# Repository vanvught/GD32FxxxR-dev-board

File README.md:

[PayPal.Me Donate](https://paypal.me/AvanVught?locale.x=nl_NL)

-----------

# GD32F103R GD32F107R GD32F207R GD32F303R GD32F407R development board

This board can be used with the `GD32F103Rx`,  `GD32F303Rx` and the `GD32F107Rx` , `GD32F207Rx`, `GD32F407Rx` (Ethernet) MCU's. 

Please note that the crystal for the `GD32F107Rx`, `GD32F207Rx` and the `GD32F407Rx` is `25MHz` and the crystal for the `GD32F103Rx` and the  `GD32F303Rx` is `8MHz`.

The 2x13 header is pin compatible with the Orange Pi Zero and Raspberry Pi boards. 

Details -> [https://www.gd32-dmx.org/dev-board.html](https://www.gd32-dmx.org/dev-board.html)

# Add-on
Pixel 8x 4 Universes for the `GD32F207RG` / `GD32F407RE`

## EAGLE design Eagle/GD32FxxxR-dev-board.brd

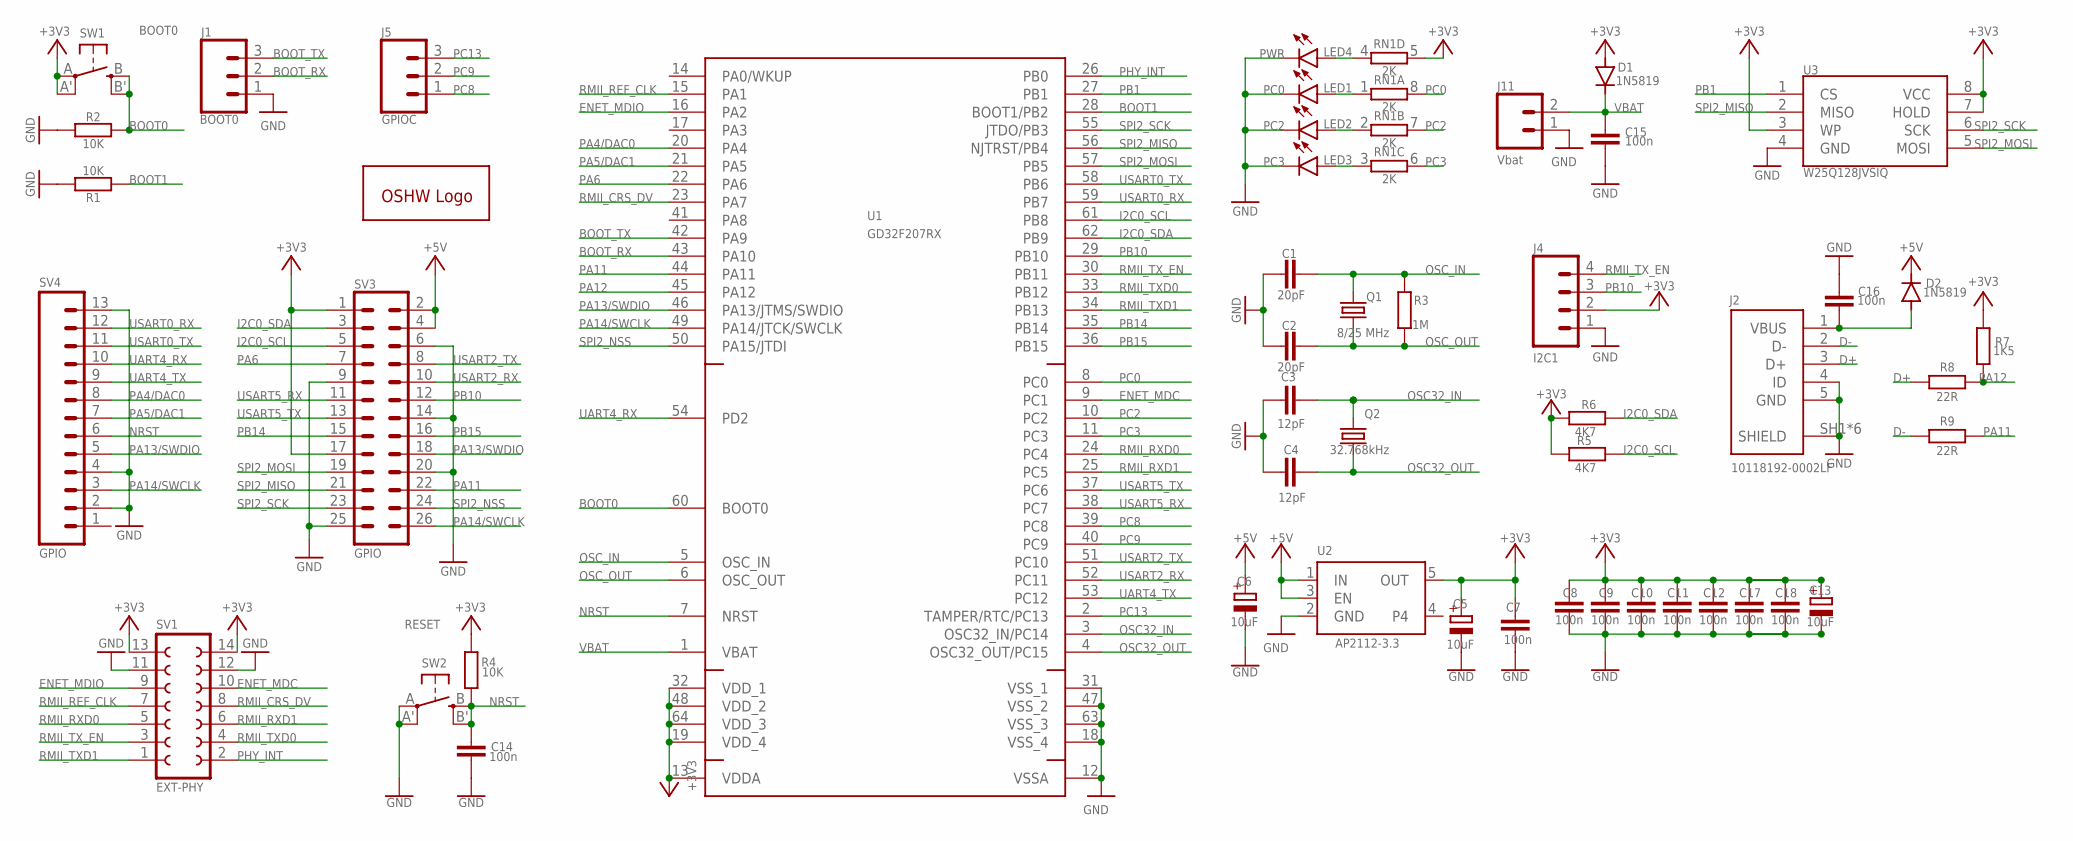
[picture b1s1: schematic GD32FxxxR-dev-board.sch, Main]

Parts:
C1, C2: 20pF; C0603; JLCPCB C38523
C3, C4: 12pF; C0603; JLCPCB C38523
C5, C6, C13: 10uF; A/3216-18R; JLCPCB C7171
C7, C8, C9, C10, C11, C12, C14, C15, C16, C17, C18: 100n; C0603; JLCPCB C14663
D1, D2: 1N5819; SOD323-R; JLCPCB C191023
GOLD_ORB_SM1: OSHWLOGOLOGO5MM; OSHW_5MM
J1: BOOT0; 1X03
J2: 10118192-0002LF; JLCPCB C2972784
J4: I2C1; 1X04
J5: GPIOC; 1X03
J11: Vbat; 1X02_NO_SILK
LED1: PC0; CHIP-LED0603
LED2: PC2; CHIP-LED0603
LED3: PC3; CHIP-LED0603
LED4: PWR; CHIP-LED0603
Q1: 8/25 MHz; CSM-7X-DU
Q2: 32.768kHz; 3.2X1.5; JLCPCB 32.768kHz
R1, R2, R4: 10K; R0603; JLCPCB C25804
R3: 1M; R0603; JLCPCB C22935
R5, R6: 4K7; R0603; JLCPCB C23162
R7: 1K5; R0603; JLCPCB C4190
R8, R9: 22R; R0603; JLCPCB C23345
RN1: 2K; 4X0402ARV341; JLCPCB C44891
SV1: EXT-PHY; FE07-2W
SV3: GPIO; MA13-2
SV4: GPIO; 1X13
SW1: BOOT0; EVQ-Q2; JLCPCB C221880
SW2: RESET; EVQ-Q2
U1: GD32F207RX; LQFP64
U2: AP2112-3.3; SOT23-5; JLCPCB C51118
U3: W25Q128JVSIQ; SO08-EIAJ; JLCPCB C97521

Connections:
+3V3: C5.+, C7.1, C8.1, C9.1, C10.1, C11.1, C12.1, C13.+, C17.1, C18.1, D1.A, J4.2, R4.2, R5.2, R6.2, R7.2, RN1.5 (2), SV1.13, SV1.14, SV3.1, SV3.17, SW1.A, SW1.A' (P1), U1.13 (VDDA), U1.19 (VDD_4), U1.32 (VDD_1), U1.48 (VDD_2), U1.64 (VDD_3), U2.5 (OUT), U3.3 (WP), U3.7 (HOLD), U3.8 (VCC)
+5V: C6.+, D2.C, SV3.2, SV3.4, U2.1 (IN), U2.3 (EN)
BOOT0: R2.2, SW1.B (S), SW1.B' (S1), U1.60 (BOOT0)
BOOT1: R1.1, U1.28 (BOOT1/PB2)
BOOT_RX: J1.2, U1.43 (PA10)
BOOT_TX: J1.3, U1.42 (PA9)
D+: J2.3 (D+), R8.1
D-: J2.2 (D-), R9.1
ENET_MDC: SV1.10, U1.9 (PC1)
ENET_MDIO: SV1.9, U1.16 (PA2)
GND: C1.1, C2.1, C3.1, C4.1, C5.-, C6.-, C7.2, C8.2, C9.2, C10.2, C11.2, C12.2, C13.-, C14.2, C15.2, C16.1, C17.2, C18.2, J1.1, J2.4 (ID), J2.5 (GND), J2.SH1 (SHIELD), J2.SH2 (SHIELD), J2.SH3 (SHIELD), J2.SH4 (SHIELD), J2.SH5 (SHIELD), J2.SH6 (SHIELD), J4.1, J11.1, LED1.C, LED2.C, LED3.C, LED4.C, R1.2, R2.1, SV1.11, SV1.12, SV3.6, SV3.9, SV3.14, SV3.20, SV3.25, SV4.2, SV4.4, SV4.13, SW2.A, SW2.A' (P1), U1.12 (VSSA), U1.18 (VSS_4), U1.31 (VSS_1), U1.47 (VSS_2), U1.63 (VSS_3), U2.2 (GND), U3.4 (GND)
I2C0_SCL: R5.1, SV3.5, U1.61 (PB8)
I2C0_SDA: R6.1, SV3.3, U1.62 (PB9)
unnamed: LED1.A, RN1.1
unnamed: LED2.A, RN1.2 (1)
unnamed: LED3.A, RN1.3 (1)
unnamed: LED4.A, RN1.4 (1)
NRST: C14.1, R4.1, SV4.6, SW2.B (S), SW2.B' (S1), U1.7 (NRST)
OSC32_IN: C3.2, Q2.2, U1.3 (OSC32_IN/PC14)
OSC32_OUT: C4.2, Q2.1, U1.4 (OSC32_OUT/PC15)
OSC_IN: C1.2, Q1.2, R3.1, U1.5 (OSC_IN)
OSC_OUT: C2.2, Q1.1, R3.2, U1.6 (OSC_OUT)
PA4/DAC0: SV4.8, U1.20 (PA4)
PA5/DAC1: SV4.7, U1.21 (PA5)
PA6: SV3.7, U1.22 (PA6)
PA11: R9.2, SV3.22, U1.44 (PA11)
PA12: R7.1, R8.2, U1.45 (PA12)
PA13/SWDIO: SV3.18, SV4.5, U1.46 (PA13/JTMS/SWDIO)
PA14/SWCLK: SV3.26, SV4.3, U1.49 (PA14/JTCK/SWCLK)
PB1: U1.27 (PB1), U3.1 (CS)
PB10: J4.3, SV3.12, U1.29 (PB10)
PB14: SV3.15, U1.35 (PB14)
PB15: SV3.16, U1.36 (PB15)
PC0: RN1.8 (2), U1.8 (PC0)
PC2: RN1.7 (2), U1.10 (PC2)
PC3: RN1.6 (2), U1.11 (PC3)
PC8: J5.1, U1.39 (PC8)
PC9: J5.2, U1.40 (PC9)
PC13: J5.3, U1.2 (TAMPER/RTC/PC13)
PHY_INT: SV1.2, U1.26 (PB0)
RMII_CRS_DV: SV1.8, U1.23 (PA7)
RMII_REF_CLK: SV1.7, U1.15 (PA1)
RMII_RXD0: SV1.5, U1.24 (PC4)
RMII_RXD1: SV1.6, U1.25 (PC5)
RMII_TXD0: SV1.4, U1.33 (PB12)
RMII_TXD1: SV1.1, U1.34 (PB13)
RMII_TX_EN: J4.4, SV1.3, U1.30 (PB11)
SPI2_MISO: SV3.21, U1.56 (NJTRST/PB4), U3.2 (MISO)
SPI2_MOSI: SV3.19, U1.57 (PB5), U3.5 (MOSI)
SPI2_NSS: SV3.24, U1.50 (PA15/JTDI)
SPI2_SCK: SV3.23, U1.55 (JTDO/PB3), U3.6 (SCK)
UART4_RX: SV4.10, U1.54 (PD2)
UART4_TX: SV4.9, U1.53 (PC12)
USART0_RX: SV4.12, U1.59 (PB7)
USART0_TX: SV4.11, U1.58 (PB6)
USART2_RX: SV3.10, U1.52 (PC11)
USART2_TX: SV3.8, U1.51 (PC10)
USART5_RX: SV3.11, U1.38 (PC7)
USART5_TX: SV3.13, U1.37 (PC6)
VBAT: C15.1, D1.C, J11.2, U1.1 (VBAT)
VBUS: C16.2, D2.A, J2.1 (VBUS)

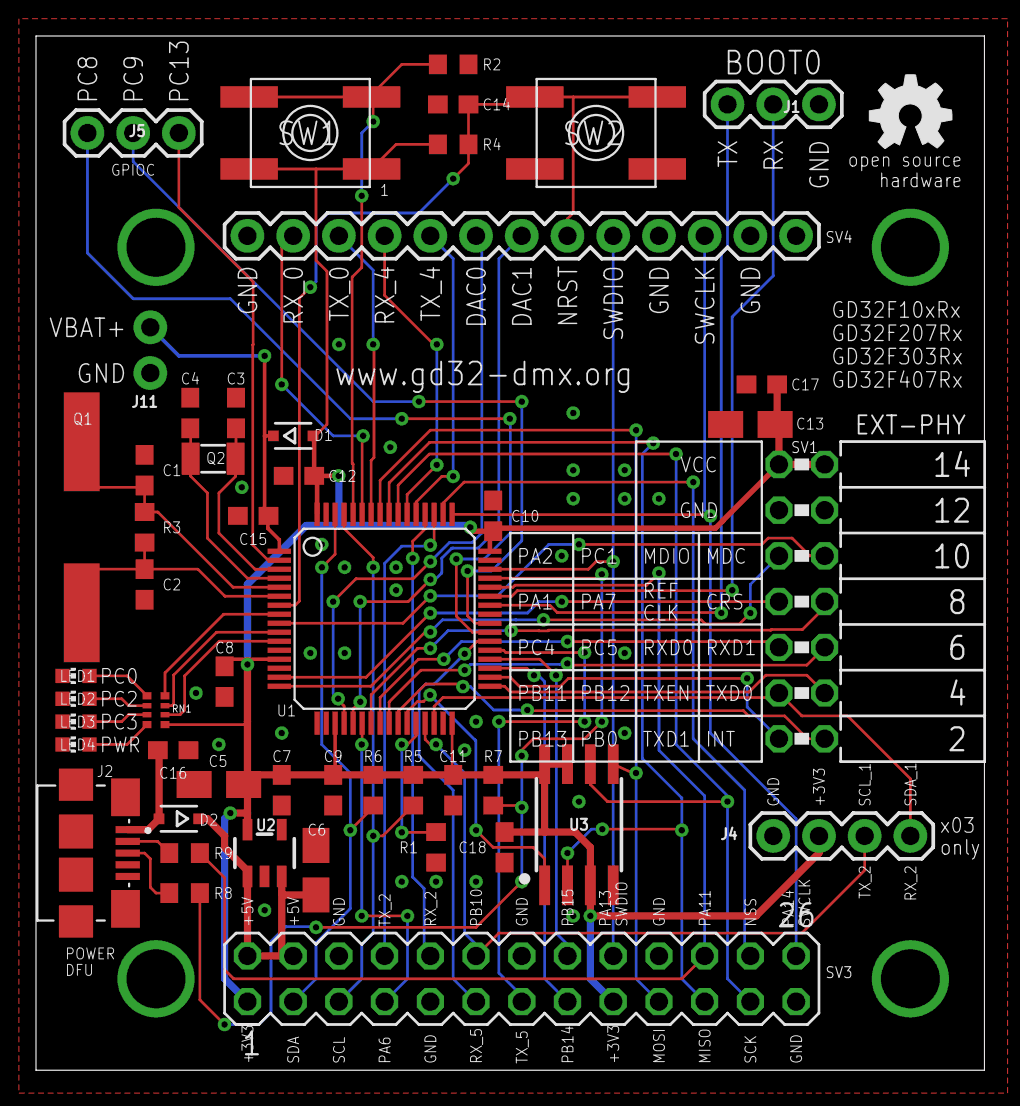
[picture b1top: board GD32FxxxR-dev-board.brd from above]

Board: 2 copper layers, 52.7 x 57.5 mm, 50 parts (0 on the bottom side), 61 nets.

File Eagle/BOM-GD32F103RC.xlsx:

Qty | Designator | Footprint | Comment | LCSC Part #
2 | C1, C2 | C0603 | 20pF | C1648
2 | C3, C4 | C0603 | 12pF | C38523
3 | C5, C6, C13 | A/3216-18R | 10uF | C7171
11 | C7, C8, C9, C10, C11, C12, C14, C15, C16, C17, C18 | C0603 | 100n | C14663
4 | LED1, LED2, LED3, LED4 | CHIP-LED0603 | LEDCHIP-LED0603 | C72043
2 | D1, D2 | SOD323-R | 1N5819 | C191023
3 | R1, R2, R4 | R0603 | 10K | C25804
1 | R3 | R0603 | 1M | C22935
2 | R5,R6 | R0603 | 4K7 | C116693
1 | R7 | R0603 | 1K5 | C4190
2 | R8, R9 | R0603 | 22R | C23345
1 | RN1 | 4X0402ARV341 | 2K | C44891
1 | U1 | LQFP64 | GD32F103RC | C80687
1 | U2 | SOT23-5 | TPRT9013-33GB | C587158
1 | U3 | SOIC-8_208mil | W25Q128 | C97521
1 | J2 | 10118192-0002LF | USB-B-MICRO-SMD | C2972784
1 | Q1 | HC-49S-SMD-2P | 8 Mhz Crystal 20pF | C12674
1 | Q2 | FC-12M | 32.768kHz Crystal 12.5pF | C32346
2 | SW1, SW2 | ﻿EVQ-Q2 | SPST 6*6mm Tactile Switch | C221880
42

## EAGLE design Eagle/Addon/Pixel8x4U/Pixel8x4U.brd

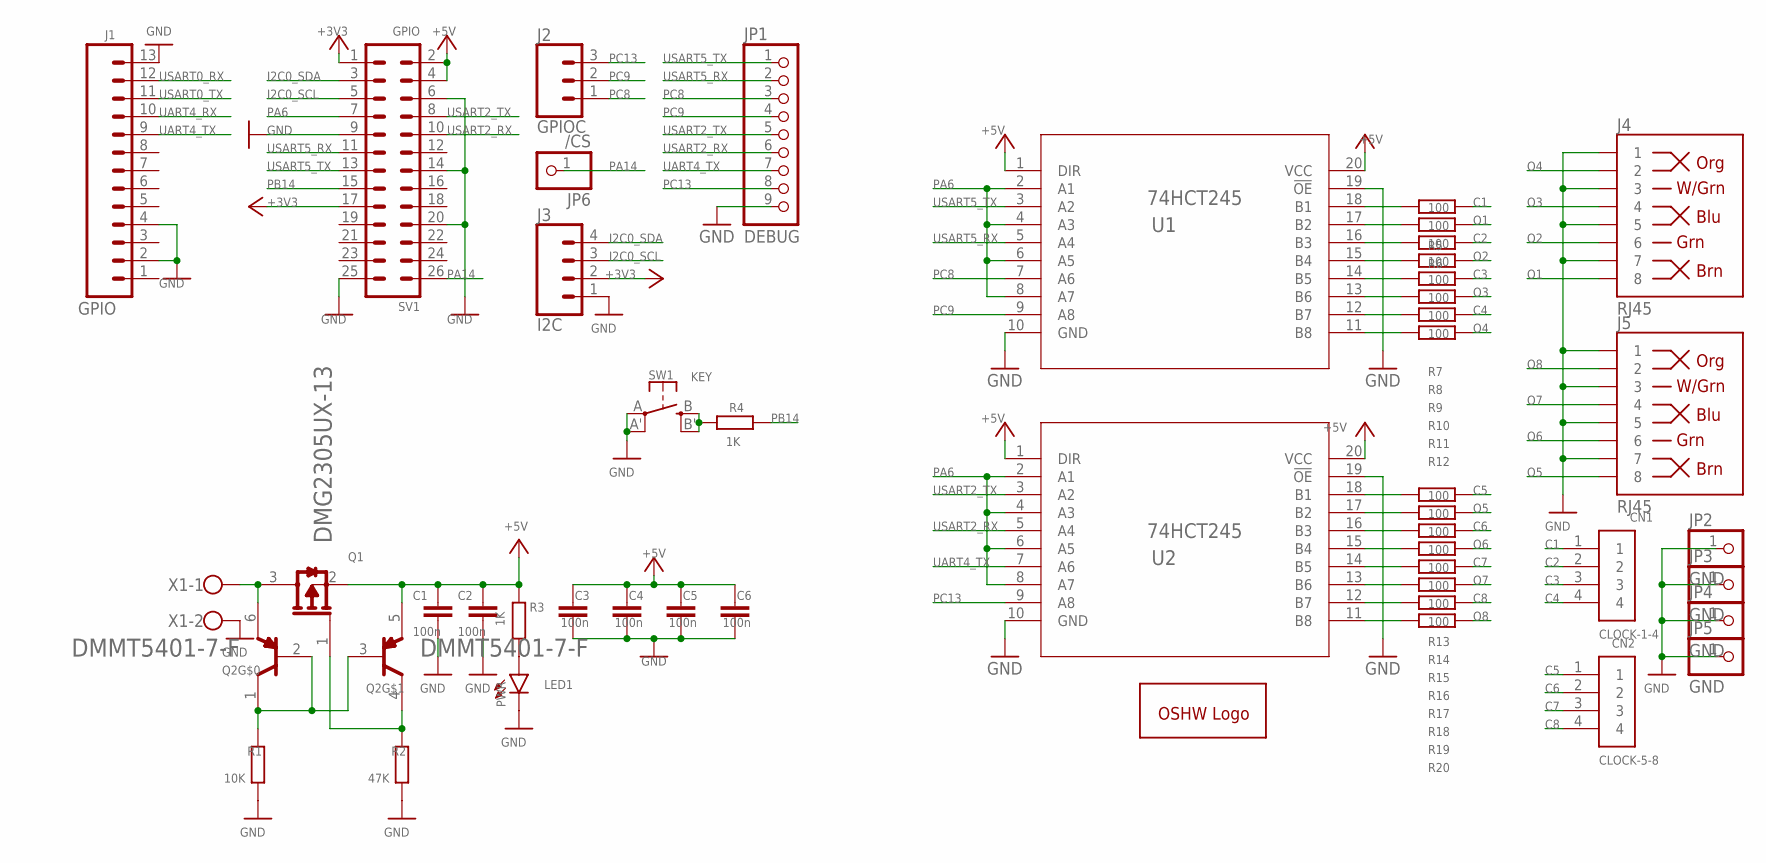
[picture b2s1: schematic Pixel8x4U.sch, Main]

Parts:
C1, C2, C3, C4, C5, C6: 100n; C0603
CN1: CLOCK-1-4; 1X04-CLEANBIG
CN2: CLOCK-5-8; 1X04-CLEANBIG
GOLD_ORB_SM1: OSHWLOGOLOGO5MM; OSHW_5MM
J1: GPIO; 1X13
J2: GPIOC; 1X03
J3: I2C; 1X04
J4, J5: RJ45; RJ45-8
JP1: DEBUG; 1X09
JP2, JP3, JP4, JP5: GND; 1X01-CLEANBIG
JP6: /CS; 1X01-CLEANBIG
LED1: PWR; CHIP-LED0603
Q1: DIODES_INC._DMG2305UX-13DIODES_INC._DMG2305UX-13_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; DIODES_INC._DMG2305UX-13_0
Q2: DMMT5401-7-F_0_0; DIODES_DMMT5401-7-F_0
R1: 10K; R0402
R2: 47K; R0402
R3, R4: 1K; R0402
R5, R6, R7, R8, R9, R10, R11, R12, R13, R14, R15, R16, R17, R18, R19, R20: 100; R0402
SV1: GPIO; MA13-2
SW1: KEY; EVQ-Q2
U1, U2: 74HCT245; PW20
X1: W237-102

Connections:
+3V3: J3.2, SV1.1, SV1.17
+5V: C1.1, C2.1, C3.1, C4.1, C5.1, C6.1, Q1.2 (S), Q2.5 (E2), R3.1, SV1.2, SV1.4, U1.1 (DIR), U1.20 (VCC), U2.1 (DIR), U2.20 (VCC)
C1: CN1.1, R5.2
C2: CN1.2, R7.2
C3: CN1.3, R9.2
C4: CN1.4, R11.2
C5: CN2.1, R13.2
C6: CN2.2, R15.2
C7: CN2.3, R17.2
C8: CN2.4, R19.2
GND: C1.2, C2.2, C3.2, C4.2, C5.2, C6.2, J1.2, J1.4, J1.13, J3.1, J4.1, J4.3, J4.5, J4.7, J5.1, J5.3, J5.5, J5.7, JP1.9, JP2.1, JP3.1, JP4.1, JP5.1, LED1.C, R1.1, R2.1, SV1.6, SV1.9, SV1.14, SV1.20, SV1.25, SW1.A, SW1.A' (P1), U1.10 (GND), U1.19 (!OE), U2.10 (GND), U2.19 (!OE), X1.2
I2C0_SCL: J3.3, SV1.5
I2C0_SDA: J3.4, SV1.3
unnamed: Q2.1 (C1), Q2.2 (B1), Q2.3 (B2), R1.2
unnamed: Q1.3 (D), Q2.6 (E1), X1.1
unnamed: Q1.1 (G), Q2.4 (C2), R2.2
unnamed: R4.1, SW1.B (S), SW1.B' (S1)
unnamed: R6.1, U1.17 (B2)
unnamed: R12.1, U1.11 (B8)
unnamed: R10.1, U1.13 (B6)
unnamed: R8.1, U1.15 (B4)
unnamed: R5.1, U1.18 (B1)
unnamed: R7.1, U1.16 (B3)
unnamed: R14.1, U2.17 (B2)
unnamed: R16.1, U2.15 (B4)
unnamed: R18.1, U2.13 (B6)
unnamed: LED1.A, R3.2
unnamed: R20.1, U2.11 (B8)
unnamed: R9.1, U1.14 (B5)
unnamed: R11.1, U1.12 (B7)
unnamed: R13.1, U2.18 (B1)
unnamed: R15.1, U2.16 (B3)
unnamed: R17.1, U2.14 (B5)
unnamed: R19.1, U2.12 (B7)
O1: J4.8, R6.2
O2: J4.6, R8.2
O3: J4.4, R10.2
O4: J4.2, R12.2
O5: J5.8, R14.2
O6: J5.6, R16.2
O7: J5.4, R18.2
O8: J5.2, R20.2
PA6: SV1.7, U1.2 (A1), U1.4 (A3), U1.6 (A5), U1.8 (A7), U2.2 (A1), U2.4 (A3), U2.6 (A5), U2.8 (A7)
PA14: JP6.1, SV1.26
PB14: R4.2, SV1.15
PC8: J2.1, JP1.3, U1.7 (A6)
PC9: J2.2, JP1.4, U1.9 (A8)
PC13: J2.3, JP1.8, U2.9 (A8)
UART4_RX: J1.10
UART4_TX: J1.9, JP1.7, U2.7 (A6)
USART0_RX: J1.12
USART0_TX: J1.11
USART2_RX: JP1.6, SV1.10, U2.5 (A4)
USART2_TX: JP1.5, SV1.8, U2.3 (A2)
USART5_RX: JP1.2, SV1.11, U1.5 (A4)
USART5_TX: JP1.1, SV1.13, U1.3 (A2)

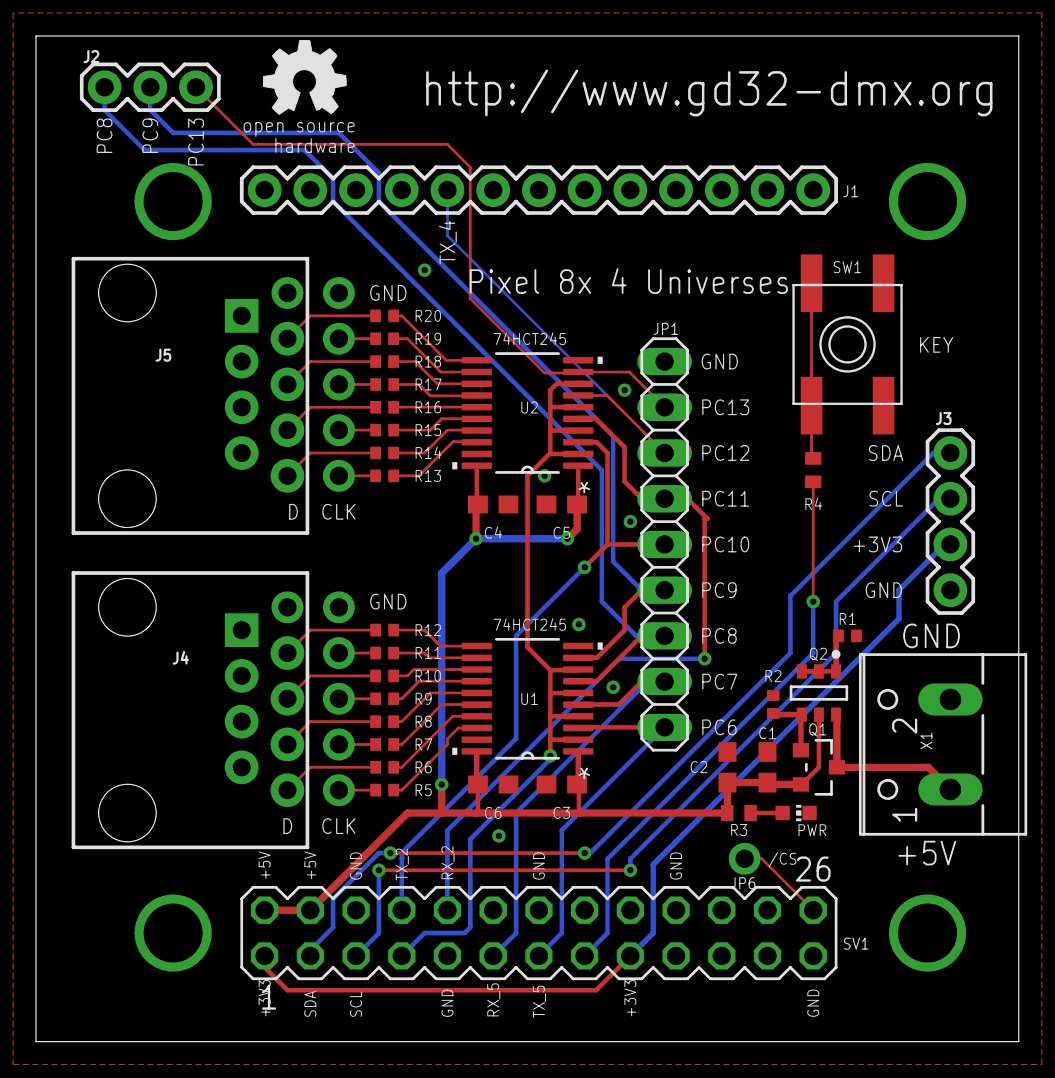
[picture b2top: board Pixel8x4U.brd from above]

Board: 2 copper layers, 54.6 x 55.9 mm, 48 parts (0 on the bottom side), 53 nets.

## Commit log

2022-03-23 Added GD32F303R
2022-10-10 Updated Add-on Pixel 8x 4 Universes
    *. Added support for clock based led chip's (for example APA102)
2022-12-25 Added SPI Flash ROM

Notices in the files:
parts and their libraries:
SparkFun-Connectors: Licensing: Creative Commons ShareAlike 4.0 International - https://creativecommons.org/licenses/by-sa/4.0
microbuilder: This work is placed in the public domain, and may be freely used for commercial and non-commercial work with the following conditions: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
